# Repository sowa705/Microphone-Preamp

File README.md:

# Microphone-Preamp
Eagle project implementing a simple microphone preamp based on TL071 op amp based on http://www.zen22142.zen.co.uk/Circuits/Audio/lf071_mic.htm
# Performance
Terrible, listen for yourself: https://www.youtube.com/watch?v=mWlRJajNbo8

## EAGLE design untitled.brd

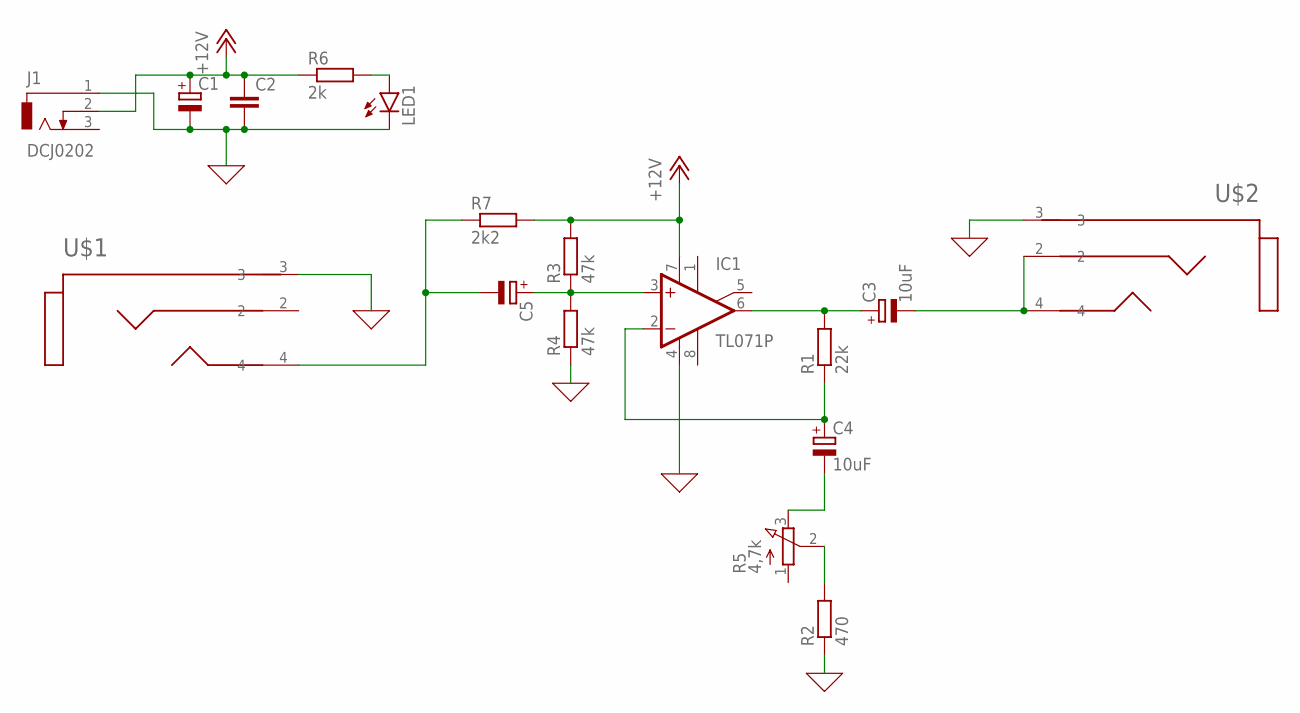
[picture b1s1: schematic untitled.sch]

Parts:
C1, C5: CPOL-EUE2,5-6E; E2,5-6E
C2: C-EU025-025X050; C025-025X050
C3, C4: 10uF; E2,5-6E
IC1: TL071P; DIL08
J1: DCJ0202
LED1: LED5MM
R1: 22k; 0207/10
R2: 470; 0207/10
R3, R4: 47k; 0207/10
R5: 4,7k; 3RP/1610N
R6: 2k; 0207/10
R7: 2k2; 0207/10
U$1, U$2: PJ321

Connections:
0: C1.-, C2.2, IC1.4 (V-), J1.1, LED1.K (C), R2.1, R4.1, U$1.3, U$2.3
+12V: C1.+, C2.1, IC1.7 (V+), J1.2, R3.2, R6.1, R7.2
unnamed: C3.+, IC1.6 (OUT), R1.2
unnamed: C4.+, IC1.2 (-IN), R1.1
unnamed: C5.+, IC1.3 (+IN), R3.1, R4.2
unnamed: C4.-, R5.3 (E)
unnamed: R2.2, R5.2 (S)
unnamed: LED1.A, R6.2
unnamed: C5.-, R7.1, U$1.4
unnamed: C3.-, U$2.2, U$2.4

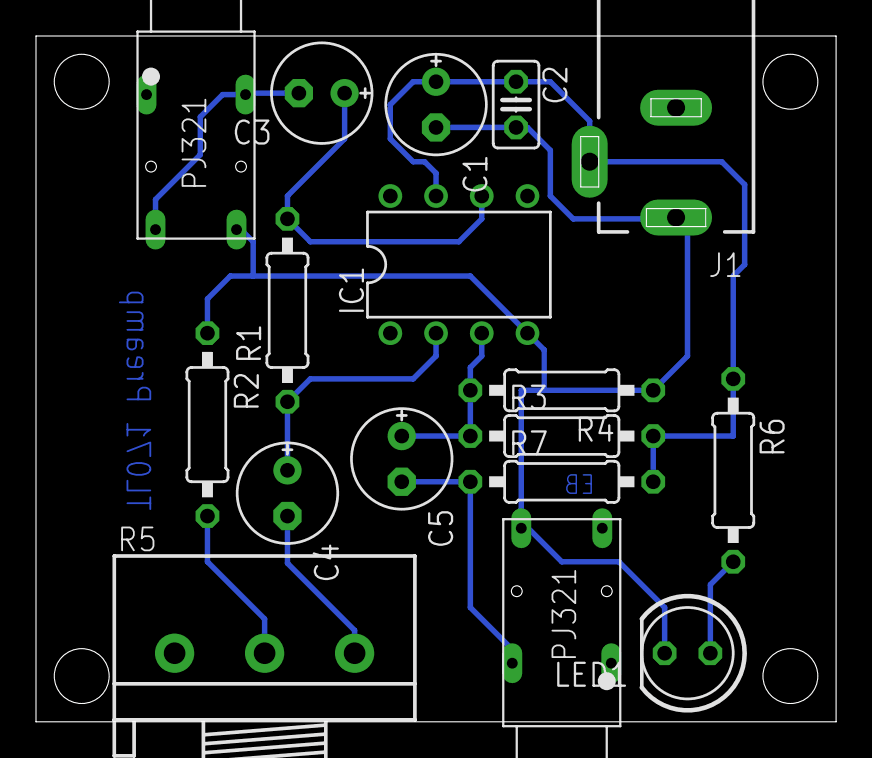
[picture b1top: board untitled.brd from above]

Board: 2 copper layers, 44.4 x 38.1 mm, 17 parts (0 on the bottom side), 10 nets.

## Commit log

2020-11-21 first version
